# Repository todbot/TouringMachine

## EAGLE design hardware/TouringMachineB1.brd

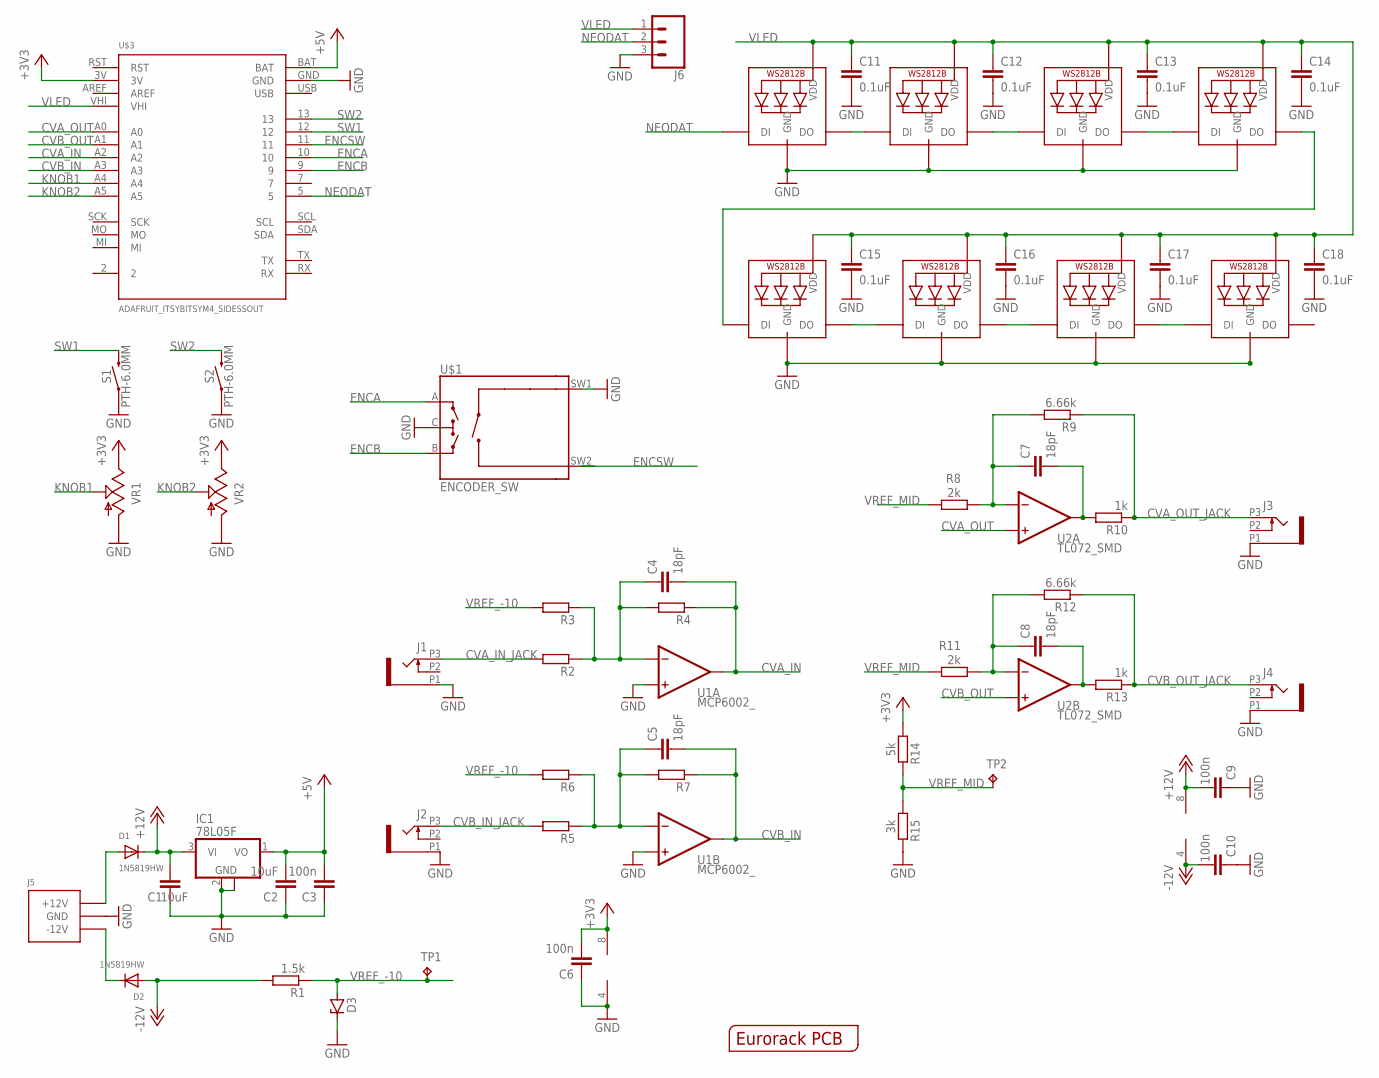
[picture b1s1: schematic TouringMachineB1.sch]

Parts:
C1, C2: 10uF; C0603
C3, C6, C9, C10: 100n; C0603
C4, C5, C7, C8: 18pF; C0603
C11, C12, C13, C14, C15, C16, C17, C18: 0.1uF; C0603
D1, D2: 1N5819HW; SOD-123
D3: ZENER-DIODESOT23; SOT23
IC1: 78L05F; SOT89
J1, J2, J3, J4: PJ301_THONKICONN6; WQP_PJ_301M6
J5: POWER_SIMPLE10-OTHERSIDE; POWER_10_LABELSOTHERSIDE
J6: CONN_03; 1X03
LED1, LED2, LED3, LED4, LED5, LED6, LED7, LED8: WS2812B5050; WS2812B
PCB1: EURORACK_PCB6HP; EURORACK6HPPCB
R1: 1.5k; R0603
R2, R3, R4, R5, R6, R7: R-EU_R0603; R0603
R8, R11: 2k; R0603
R9, R12: 6.66k; R0603
R10, R13: 1k; R0603
R14: 5k; R0603
R15: 3k; R0603
S1, S2: PTH-6.0MM; TACTILE_SWITCH_PTH_6.0MM
TP1, TP2: TPTP15R; TP15R
U1: MCP6002_; SO08
U2: TL072_SMD; SO08
U$1: ENCODER_SW
U$3: ADAFRUIT_ITSYBITSYM4_SIDESSOUT; ADAFRUIT_ITSYBITSYM4_SIDESOUT
VR1, VR2: 9MM_SNAP-IN_POT_; 9MM_SNAP-IN_POT

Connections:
+3V3: C6.2, R14.1, U1.8 (V+), U$3.3V, VR1.3 (E), VR2.3 (E)
+5V: C2.2, C3.2, IC1.1 (VO), U$3.BAT
+12V: C1.2, C9.2, D1.C, IC1.3 (VI), U2.8 (V+)
-12V: C10.2, D2.A, R1.2, U2.4 (V-)
CVA_IN: C4.2, R4.1, U1.1 (OUT), U$3.A2
CVA_IN_JACK: J1.P3 (3), R2.2
CVA_OUT: U2.3 (+IN), U$3.A0
CVA_OUT_JACK: J3.P3 (3), R9.1, R10.1
CVB_IN: C5.2, R7.1, U1.7 (OUT), U$3.A3
CVB_IN_JACK: J2.P3 (3), R5.2
CVB_OUT: U2.5 (+IN), U$3.A1
CVB_OUT_JACK: J4.P3 (3), R12.1, R13.1
ENCA: U$1.A, U$3.10
ENCB: U$1.B, U$3.9
ENCSW: U$1.SW2, U$3.11
GND: C1.1, C2.1, C3.1, C6.1, C9.1, C10.1, C11.2, C12.2, C13.2, C14.2, C15.2, C16.2, C17.2, C18.2, D3.3 (C), IC1.2 (GND), IC1.2@1 (GND), J1.P1 (1), J2.P1 (1), J3.P1 (1), J4.P1 (1), J5.3 (GND), J5.4 (GND), J5.5 (GND), J5.6 (GND), J5.7 (GND), J5.8 (GND), J6.3, LED1.3-GND (GND), LED2.3-GND (GND), LED3.3-GND (GND), LED4.3-GND (GND), LED5.3-GND (GND), LED6.3-GND (GND), LED7.3-GND (GND), LED8.3-GND (GND), R15.2, S1.1, S2.1, U1.3 (+IN), U1.4 (V-), U1.5 (+IN), U$1.C, U$1.SW1, U$3.GND, VR1.1 (A), VR2.1 (A)
KNOB1: U$3.A4, VR1.2 (S)
KNOB2: U$3.A5, VR2.2 (S)
unnamed: LED2.2-DOUT (DO), LED3.4-DIN (DI)
unnamed: LED1.2-DOUT (DO), LED2.4-DIN (DI)
unnamed: LED3.2-DOUT (DO), LED4.4-DIN (DI)
unnamed: LED5.2-DOUT (DO), LED6.4-DIN (DI)
unnamed: LED6.2-DOUT (DO), LED7.4-DIN (DI)
unnamed: LED7.2-DOUT (DO), LED8.4-DIN (DI)
unnamed: LED4.2-DOUT (DO), LED5.4-DIN (DI)
unnamed: D1.A, J5.9 (+12V), J5.10 (+12V)
unnamed: D2.C, J5.1 (-12V), J5.2 (-12V)
unnamed: C4.1, R2.1, R3.1, R4.2, U1.2 (-IN)
unnamed: C7.1, R8.1, R9.2, U2.2 (-IN)
unnamed: C7.2, R10.2, U2.1 (OUT)
unnamed: C8.1, R11.1, R12.2, U2.6 (-IN)
unnamed: C5.1, R5.1, R6.1, R7.2, U1.6 (-IN)
unnamed: C8.2, R13.2, U2.7 (OUT)
NEODAT: J6.2, LED1.4-DIN (DI), U$3.5
SW1: S1.3 (2), U$3.12
SW2: S2.3 (2), U$3.13
VLED: C11.1, C12.1, C13.1, C14.1, C15.1, C16.1, C17.1, C18.1, J6.1, LED1.1-VDD (VDD), LED2.1-VDD (VDD), LED3.1-VDD (VDD), LED4.1-VDD (VDD), LED5.1-VDD (VDD), LED6.1-VDD (VDD), LED7.1-VDD (VDD), LED8.1-VDD (VDD), U$3.VHI
VREF_-10: D3.1 (A), R1.1, R3.2, R6.2, TP1.TP
VREF_MID: R8.2, R11.2, R14.2, R15.1, TP2.TP

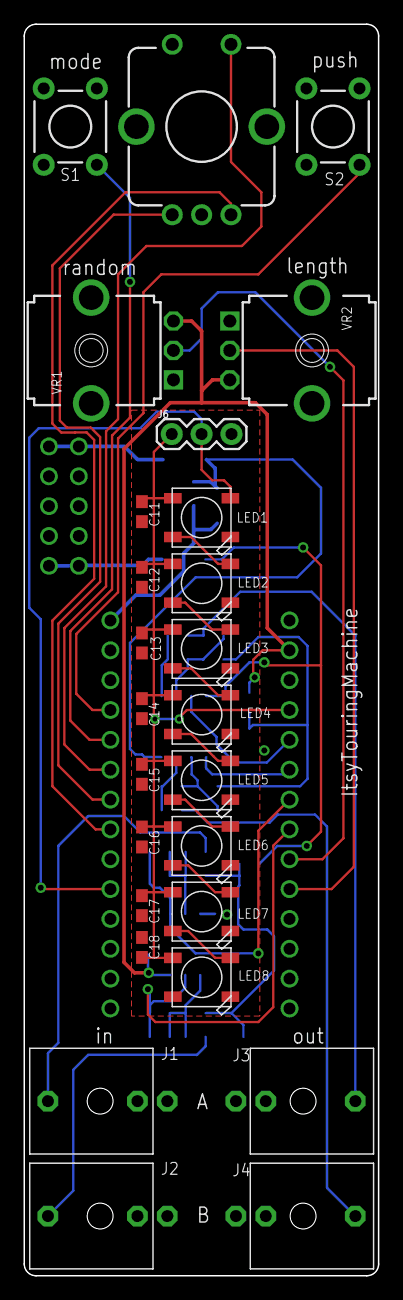
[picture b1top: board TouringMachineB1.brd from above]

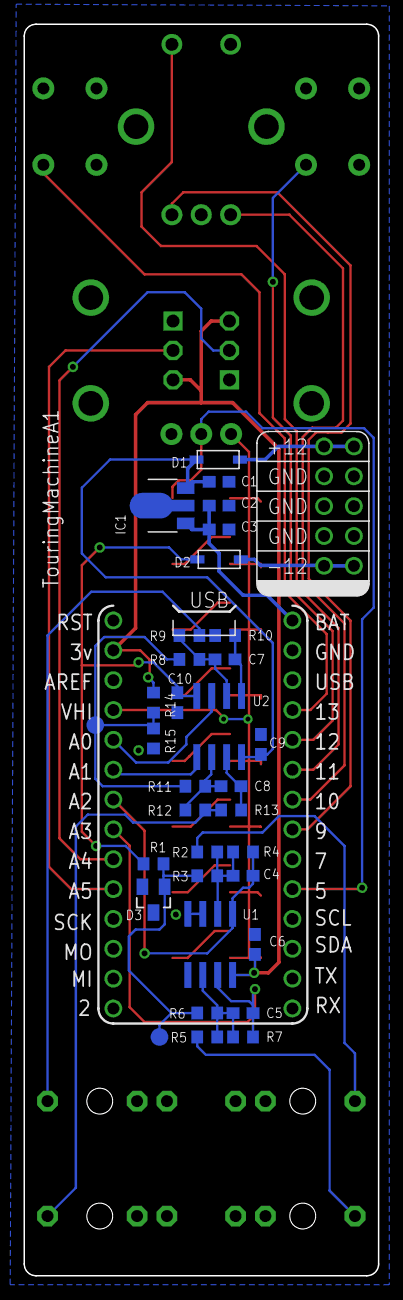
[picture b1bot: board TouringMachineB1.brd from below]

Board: 2 copper layers, 30.2 x 106.5 mm, 62 parts (35 on the bottom side), 39 nets.

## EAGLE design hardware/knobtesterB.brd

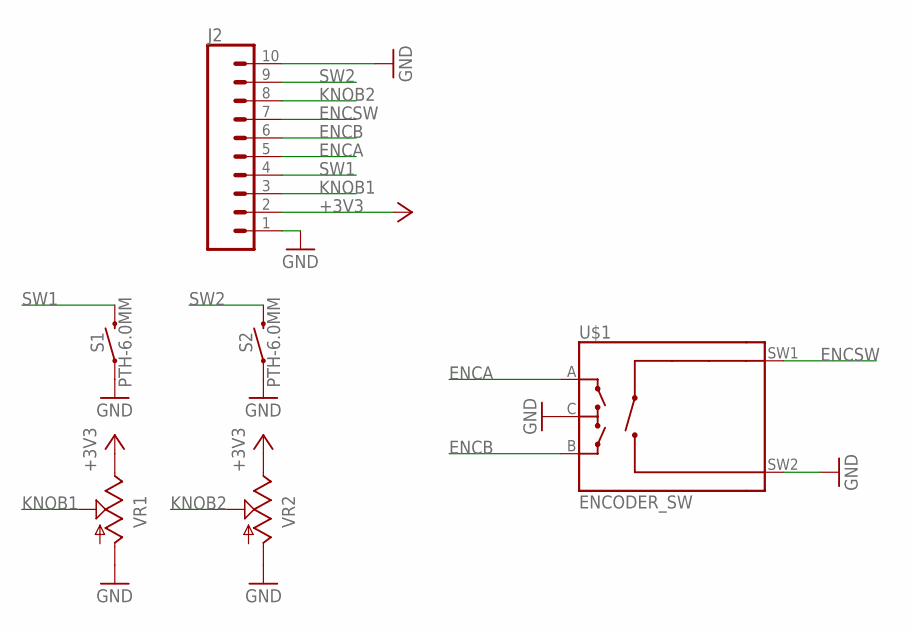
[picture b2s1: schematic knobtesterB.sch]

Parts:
J2: CONN_10"; 1X10
S1, S2: PTH-6.0MM; TACTILE_SWITCH_PTH_6.0MM
U$1: ENCODER_SW
VR1, VR2: 9MM_SNAP-IN_POT_; 9MM_SNAP-IN_POT

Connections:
+3V3: J2.2, VR1.3 (E), VR2.3 (E)
ENCA: J2.5, U$1.A
ENCB: J2.6, U$1.B
ENCSW: J2.7, U$1.SW1
GND: J2.1, J2.10, S1.1, S2.1, U$1.C, U$1.SW2, VR1.1 (A), VR2.1 (A)
KNOB1: J2.3, VR1.2 (S)
KNOB2: J2.8, VR2.2 (S)
SW1: J2.4, S1.3 (2)
SW2: J2.9, S2.3 (2)

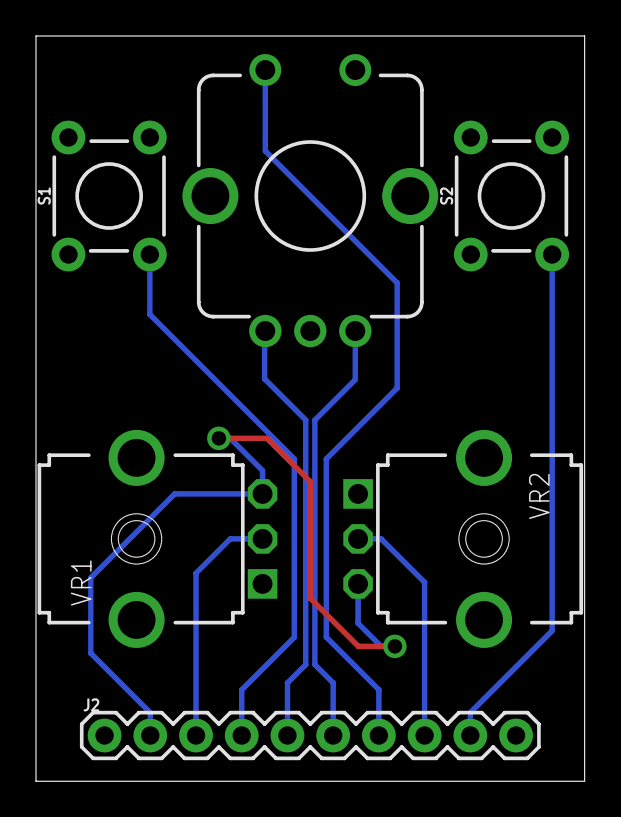
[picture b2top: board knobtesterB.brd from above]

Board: 2 copper layers, 30.5 x 41.4 mm, 6 parts (0 on the bottom side), 9 nets.

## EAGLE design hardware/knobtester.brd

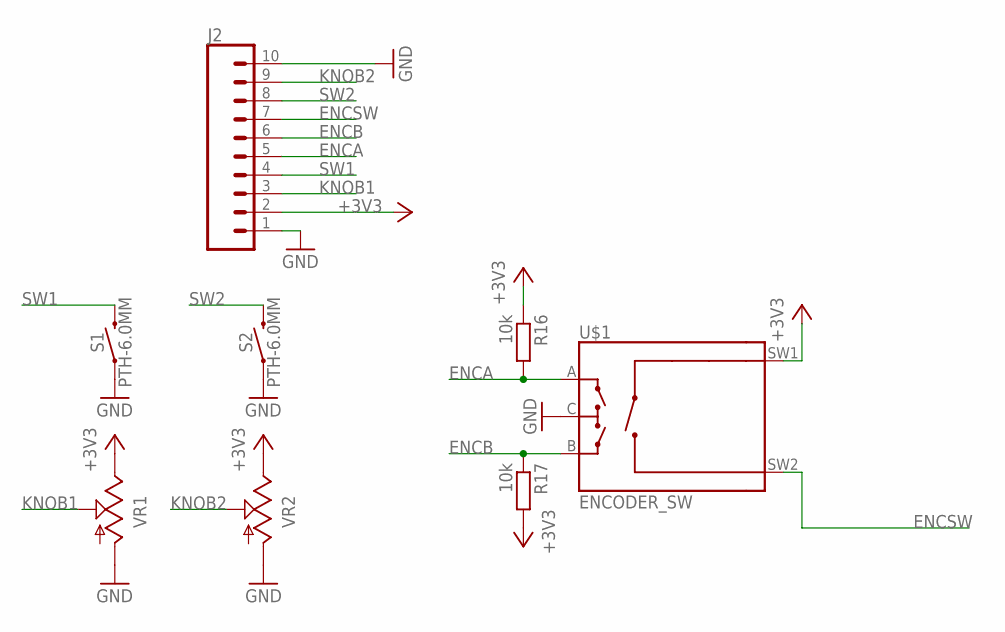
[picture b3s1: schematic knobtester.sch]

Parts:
J2: CONN_10"; 1X10
R16, R17: 10k; R0603
S1, S2: PTH-6.0MM; TACTILE_SWITCH_PTH_6.0MM
U$1: ENCODER_SW
VR1, VR2: 9MM_SNAP-IN_POT_; 9MM_SNAP-IN_POT

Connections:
+3V3: J2.2, R16.1, R17.2, U$1.SW1, VR1.3 (E), VR2.3 (E)
ENCA: J2.5, R16.2, U$1.A
ENCB: J2.6, R17.1, U$1.B
ENCSW: J2.7, U$1.SW2
GND: J2.1, J2.10, S1.1, S2.1, U$1.C, VR1.1 (A), VR2.1 (A)
KNOB1: J2.3, VR1.2 (S)
KNOB2: J2.9, VR2.2 (S)
SW1: J2.4, S1.3 (2)
SW2: J2.8, S2.3 (2)

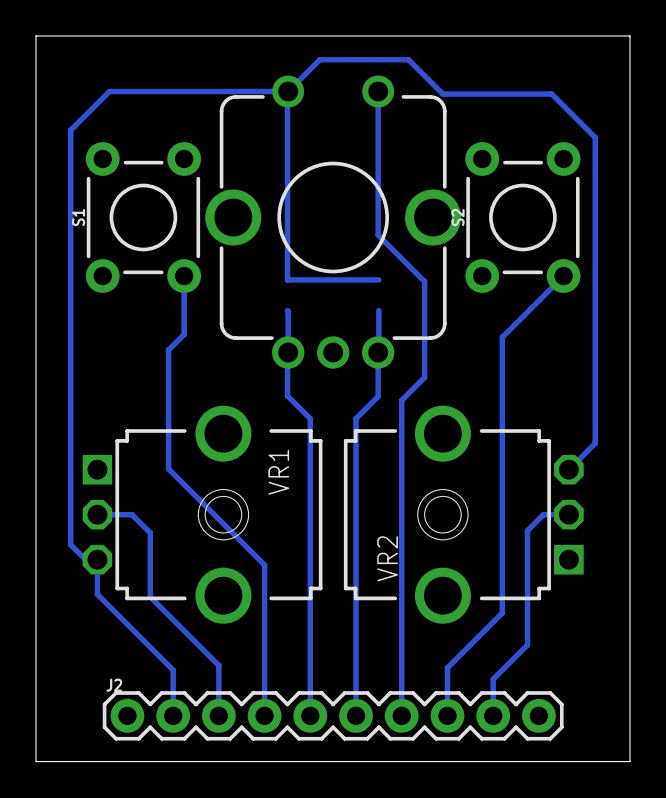
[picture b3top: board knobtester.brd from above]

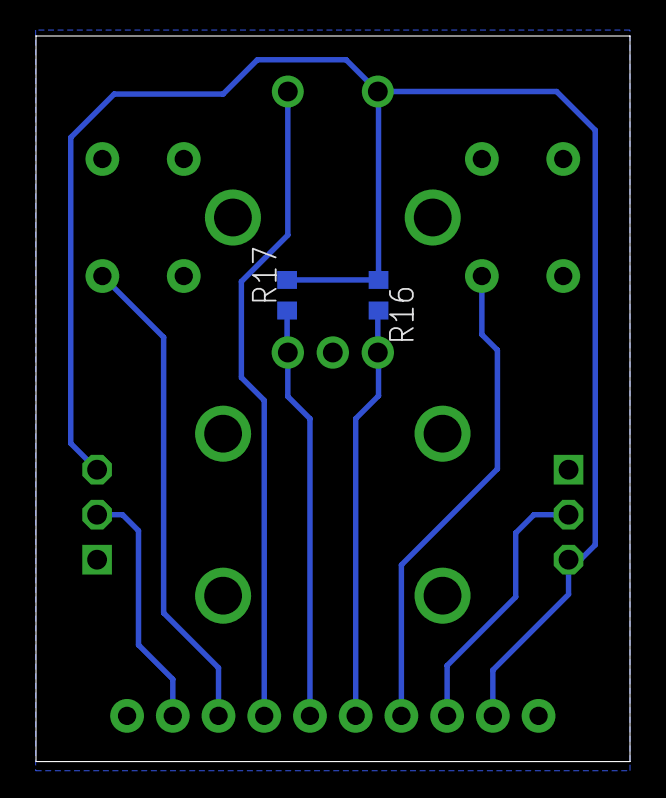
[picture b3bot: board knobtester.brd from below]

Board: 2 copper layers, 33.0 x 40.3 mm, 8 parts (2 on the bottom side), 9 nets.

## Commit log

2020-08-26 first commit!
2020-08-27 added 3d models
2020-08-30 symmetric version with full-scale outputs, still untested
2020-09-01 added knobtester
2020-09-04 new knobtesterB, better layout
2020-09-04 cleaned up UI after knobtesterA results

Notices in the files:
parts and their libraries:
SparkFun-Switches: Licensing: Creative Commons ShareAlike 4.0 International - https://creativecommons.org/licenses/by-sa/4.0
